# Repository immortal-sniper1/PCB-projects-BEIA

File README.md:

# PCB-projects
 PCB project files and skematics

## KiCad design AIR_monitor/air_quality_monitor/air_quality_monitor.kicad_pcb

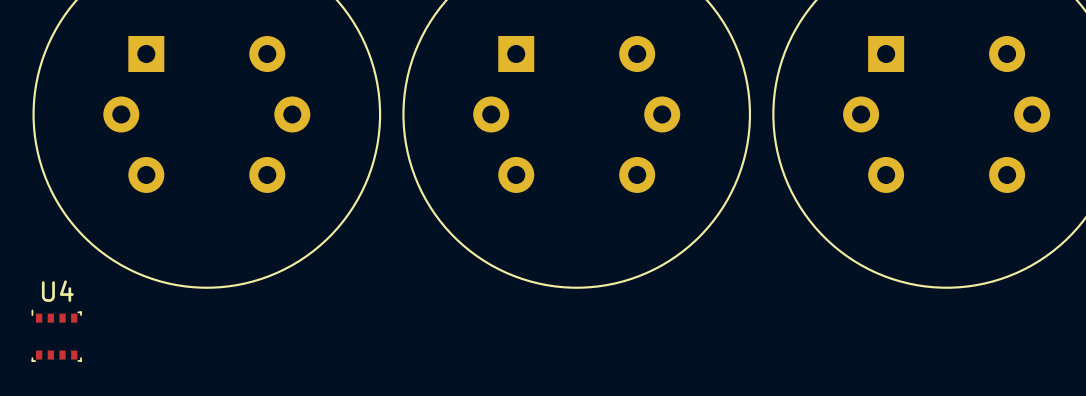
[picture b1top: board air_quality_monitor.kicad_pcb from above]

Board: 2 copper layers, 4 parts (0 on the bottom side), 5 nets, no tracks yet.

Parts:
U1: MQ-131; MQ-6
U2: MQ-136; MQ-6
U3: MQ-5/7/9; MQ-6
U4: BME280; Bosch_LGA-8_2.5x2.5mm_P0.65mm_ClockwisePinNumbering

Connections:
+5V: U1.2 (VH+), U1.4 (A2), U1.6 (A1), U2.2 (VH+), U2.4 (A2), U2.6 (A1), U3.2 (VH+), U3.4 (A2), U3.6 (A1)
GND: U1.5 (VH-), U2.5 (VH-), U3.5 (VH-), U4.1 (GND), U4.7 (GND)
unnamed: U1.1 (B1), U1.3 (B2)
unnamed: U2.1 (B1), U2.3 (B2)
unnamed: U3.1 (B1), U3.3 (B2)

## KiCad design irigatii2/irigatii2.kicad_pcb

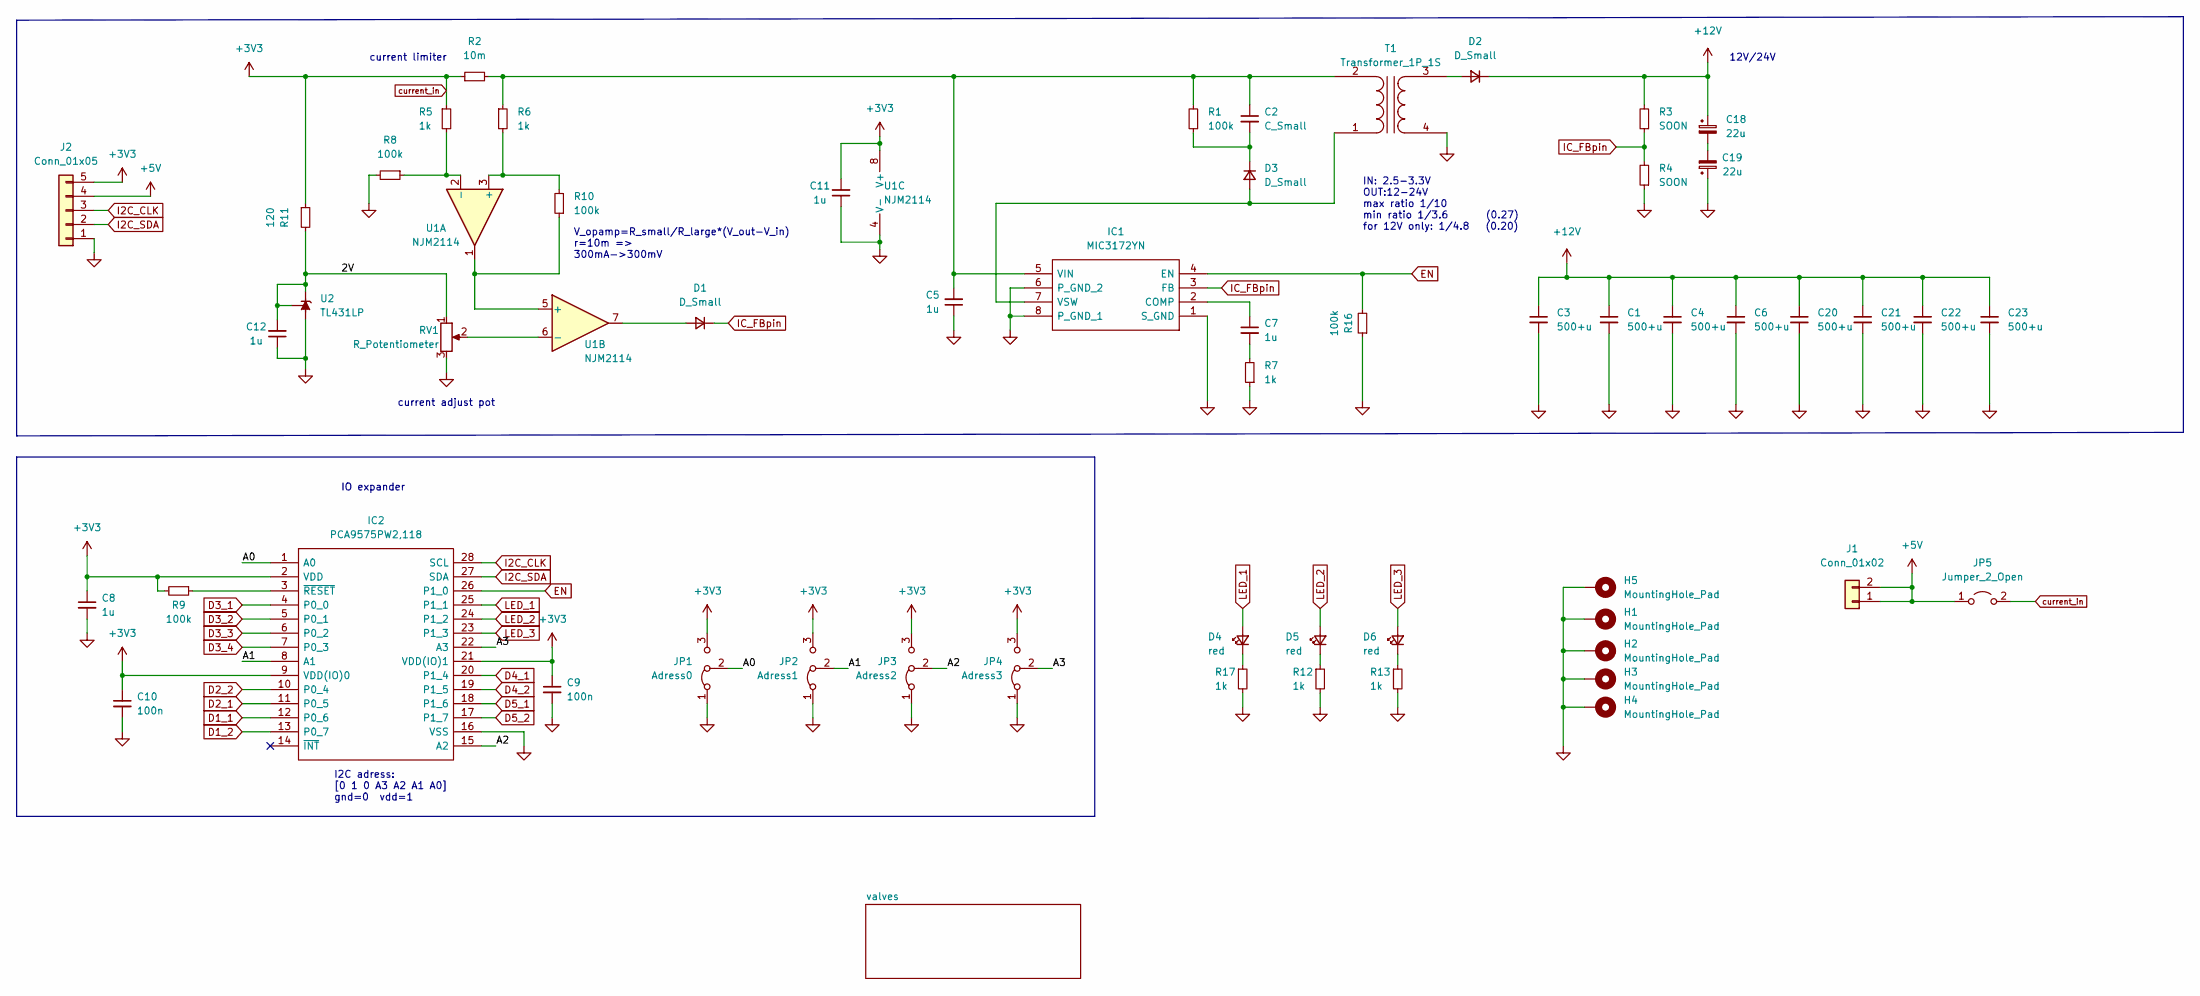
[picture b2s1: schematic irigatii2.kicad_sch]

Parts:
C1, C3, C4, C6, C20, C21, C22, C23: 500+u; CP_Radial_D13.0mm_P5.00mm
C2: C_Small; C_Disc_D4.3mm_W1.9mm_P5.00mm
C5: 1u; C_Disc_D4.3mm_W1.9mm_P5.00mm
C7, C11, C12: 1u; C_Disc_D3.8mm_W2.6mm_P2.50mm
C8: 1u; C_0805_2012Metric_Pad1.18x1.45mm_HandSolder
C9, C10: 100n; C_0805_2012Metric_Pad1.18x1.45mm_HandSolder
C18, C19: 22u; CP_Radial_D5.0mm_P2.00mm
D1, D3: D_Small; D_A-405_P5.08mm_Vertical_KathodeUp
D2: D_Small; D_A-405_P10.16mm_Horizontal
D4, D5, D6: red; LED_D5.0mm
H1, H2, H3, H4, H5: MountingHole_Pad; MountingHole_3.2mm_M3_Pad_TopBottom
IC1: MIC3172YN; DIP762W57P254L952H343Q8N; Mouser Part Number 998-MIC3172YN
IC2: PCA9575PW2,118; SOP65P640X110-28N; Mouser Part Number 771-PCA9575PW2,118
J1: Conn_01x02; PinHeader_1x02_P2.54mm_Vertical
J2: Conn_01x05; PinHeader_1x05_P2.54mm_Vertical
JP1: Adress0; SolderJumper-3_P1.3mm_Bridged12_Pad1.0x1.5mm
JP2: Adress1; SolderJumper-3_P1.3mm_Bridged12_Pad1.0x1.5mm
JP3: Adress2; SolderJumper-3_P1.3mm_Bridged12_Pad1.0x1.5mm
JP4: Adress3; SolderJumper-3_P1.3mm_Bridged12_Pad1.0x1.5mm
JP5: Jumper_2_Open; SolderJumper-2_P1.3mm_Open_Pad1.0x1.5mm
R1, R8, R9, R10, R16: 100k; R_Axial_DIN0204_L3.6mm_D1.6mm_P5.08mm_Vertical
R2: 10m; R_Axial_DIN0207_L6.3mm_D2.5mm_P10.16mm_Horizontal
R3, R4: SOON; R_Axial_DIN0207_L6.3mm_D2.5mm_P10.16mm_Horizontal
R5, R6, R7, R12, R13, R17: 1k; R_Axial_DIN0204_L3.6mm_D1.6mm_P5.08mm_Vertical
R11: 120; R_Axial_DIN0204_L3.6mm_D1.6mm_P5.08mm_Vertical
RV1: R_Potentiometer; Potentiometer_ACP_CA9-V10_Vertical
T1: Transformer_1P_1S; TRANSFORMER
U1: NJM2114; DIP-8_W7.62mm_LongPads
U2: TL431LP; TO-92_Inline

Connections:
+5V: J1.1, J1.2, J2.4, JP5.1 (A)
+12V: C1.1, C3.1, C4.1, C6.1, C18.1, C20.1, C21.1, C22.1, C23.1, D2.1 (K), R3.2; also elsewhere on the board
/2V: C12.2, R11.2, RV1.1, U2.1 (REF), U2.3 (K)
/A0: IC2.1 (A0), JP1.2 (C)
/A1: IC2.8 (A1), JP2.2 (C)
/A2: IC2.15 (A2), JP3.2 (C)
/A3: IC2.22 (A3), JP4.2 (C)
D1_1: IC2.12 (P0_6); also elsewhere on the board
D1_2: IC2.13 (P0_7); also elsewhere on the board
D2_1: IC2.11 (P0_5); also elsewhere on the board
D2_2: IC2.10 (P0_4); also elsewhere on the board
D3_1: IC2.4 (P0_0); also elsewhere on the board
D3_2: IC2.5 (P0_1); also elsewhere on the board
D3_3: IC2.6 (P0_2); also elsewhere on the board
D3_4: IC2.7 (P0_3); also elsewhere on the board
D4_1: IC2.20 (P1_4); also elsewhere on the board
D4_2: IC2.19 (P1_5); also elsewhere on the board
D5_1: IC2.18 (P1_6); also elsewhere on the board
D5_2: IC2.17 (P1_7); also elsewhere on the board
EN: IC1.4 (EN), IC2.26 (P1_0), R16.2
GND: C1.2, C3.2, C4.2, C5.1, C6.2, C8.2, C9.2, C10.2, C11.1, C12.1, C19.1, C20.2, C21.2, C22.2, C23.2, H1.1, H2.1, H3.1, H4.1, H5.1, IC1.1 (S_GND), IC1.6 (P_GND_2), IC1.8 (P_GND_1), IC2.16 (VSS), J2.1, JP1.1 (A), JP2.1 (A), JP3.1 (A), JP4.1 (A), R4.1, R7.1, R8.2, R12.2, R13.2, R16.1, R17.2, RV1.3, T1.4 (SB), U1.4 (V-), U2.2 (A); also elsewhere on the board
I2C_CLK: IC2.28 (SCL), J2.3
I2C_SDA: IC2.27 (SDA), J2.2
IC_FBpin: D1.1 (K), IC1.3 (FB), R3.1, R4.2
LED_1: D4.2 (A), IC2.25 (P1_1)
LED_2: D5.2 (A), IC2.24 (P1_2)
LED_3: D6.2 (A), IC2.23 (P1_3)
unnamed: C2.1, C5.2, IC1.5 (VIN), R1.2, R2.2, R6.1, T1.2 (AB)
unnamed: C2.2, D3.1 (K), R1.1
unnamed: C7.1, IC1.2 (COMP)
unnamed: C7.2, R7.2
unnamed: C18.2, C19.2
unnamed: D1.2 (A), U1.7
unnamed: D2.2 (A), T1.3 (SA)
unnamed: D3.2 (A), IC1.7 (VSW), T1.1 (AA)
unnamed: D4.1 (K), R17.1
unnamed: D5.1 (K), R12.1
unnamed: D6.1 (K), R13.1
unnamed: IC2.3 (~RESET), R9.1
unnamed: R5.2, R8.1, U1.2 (-)
unnamed: R10.1, U1.1, U1.5 (+)
unnamed: R6.2, R10.2, U1.3 (+)
unnamed: RV1.2, U1.6 (-)
current_in: C8.1, C9.1, C10.1, C11.2, IC2.2 (VDD), IC2.9 (VDD(IO)0), IC2.21 (VDD(IO)1), J2.5, JP1.3 (B), JP2.3 (B), JP3.3 (B), JP4.3 (B), JP5.2 (B), R2.1, R5.1, R9.2, R11.1, U1.8 (V+)

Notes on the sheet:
current adjust pot
V_opamp=R_small/R_large*(V_out-V_in) r=10m => 300mA->300mV
current limiter
I2C adress: [0 1 0 A3 A2 A1 A0] gnd=0 vdd=1
12V/24V
IN: 2.5-3.3V OUT:12-24V max ratio 1/10 min ratio 1/3.6 (0.27) for 12V only: 1/4.8 (0.20)
IO expander

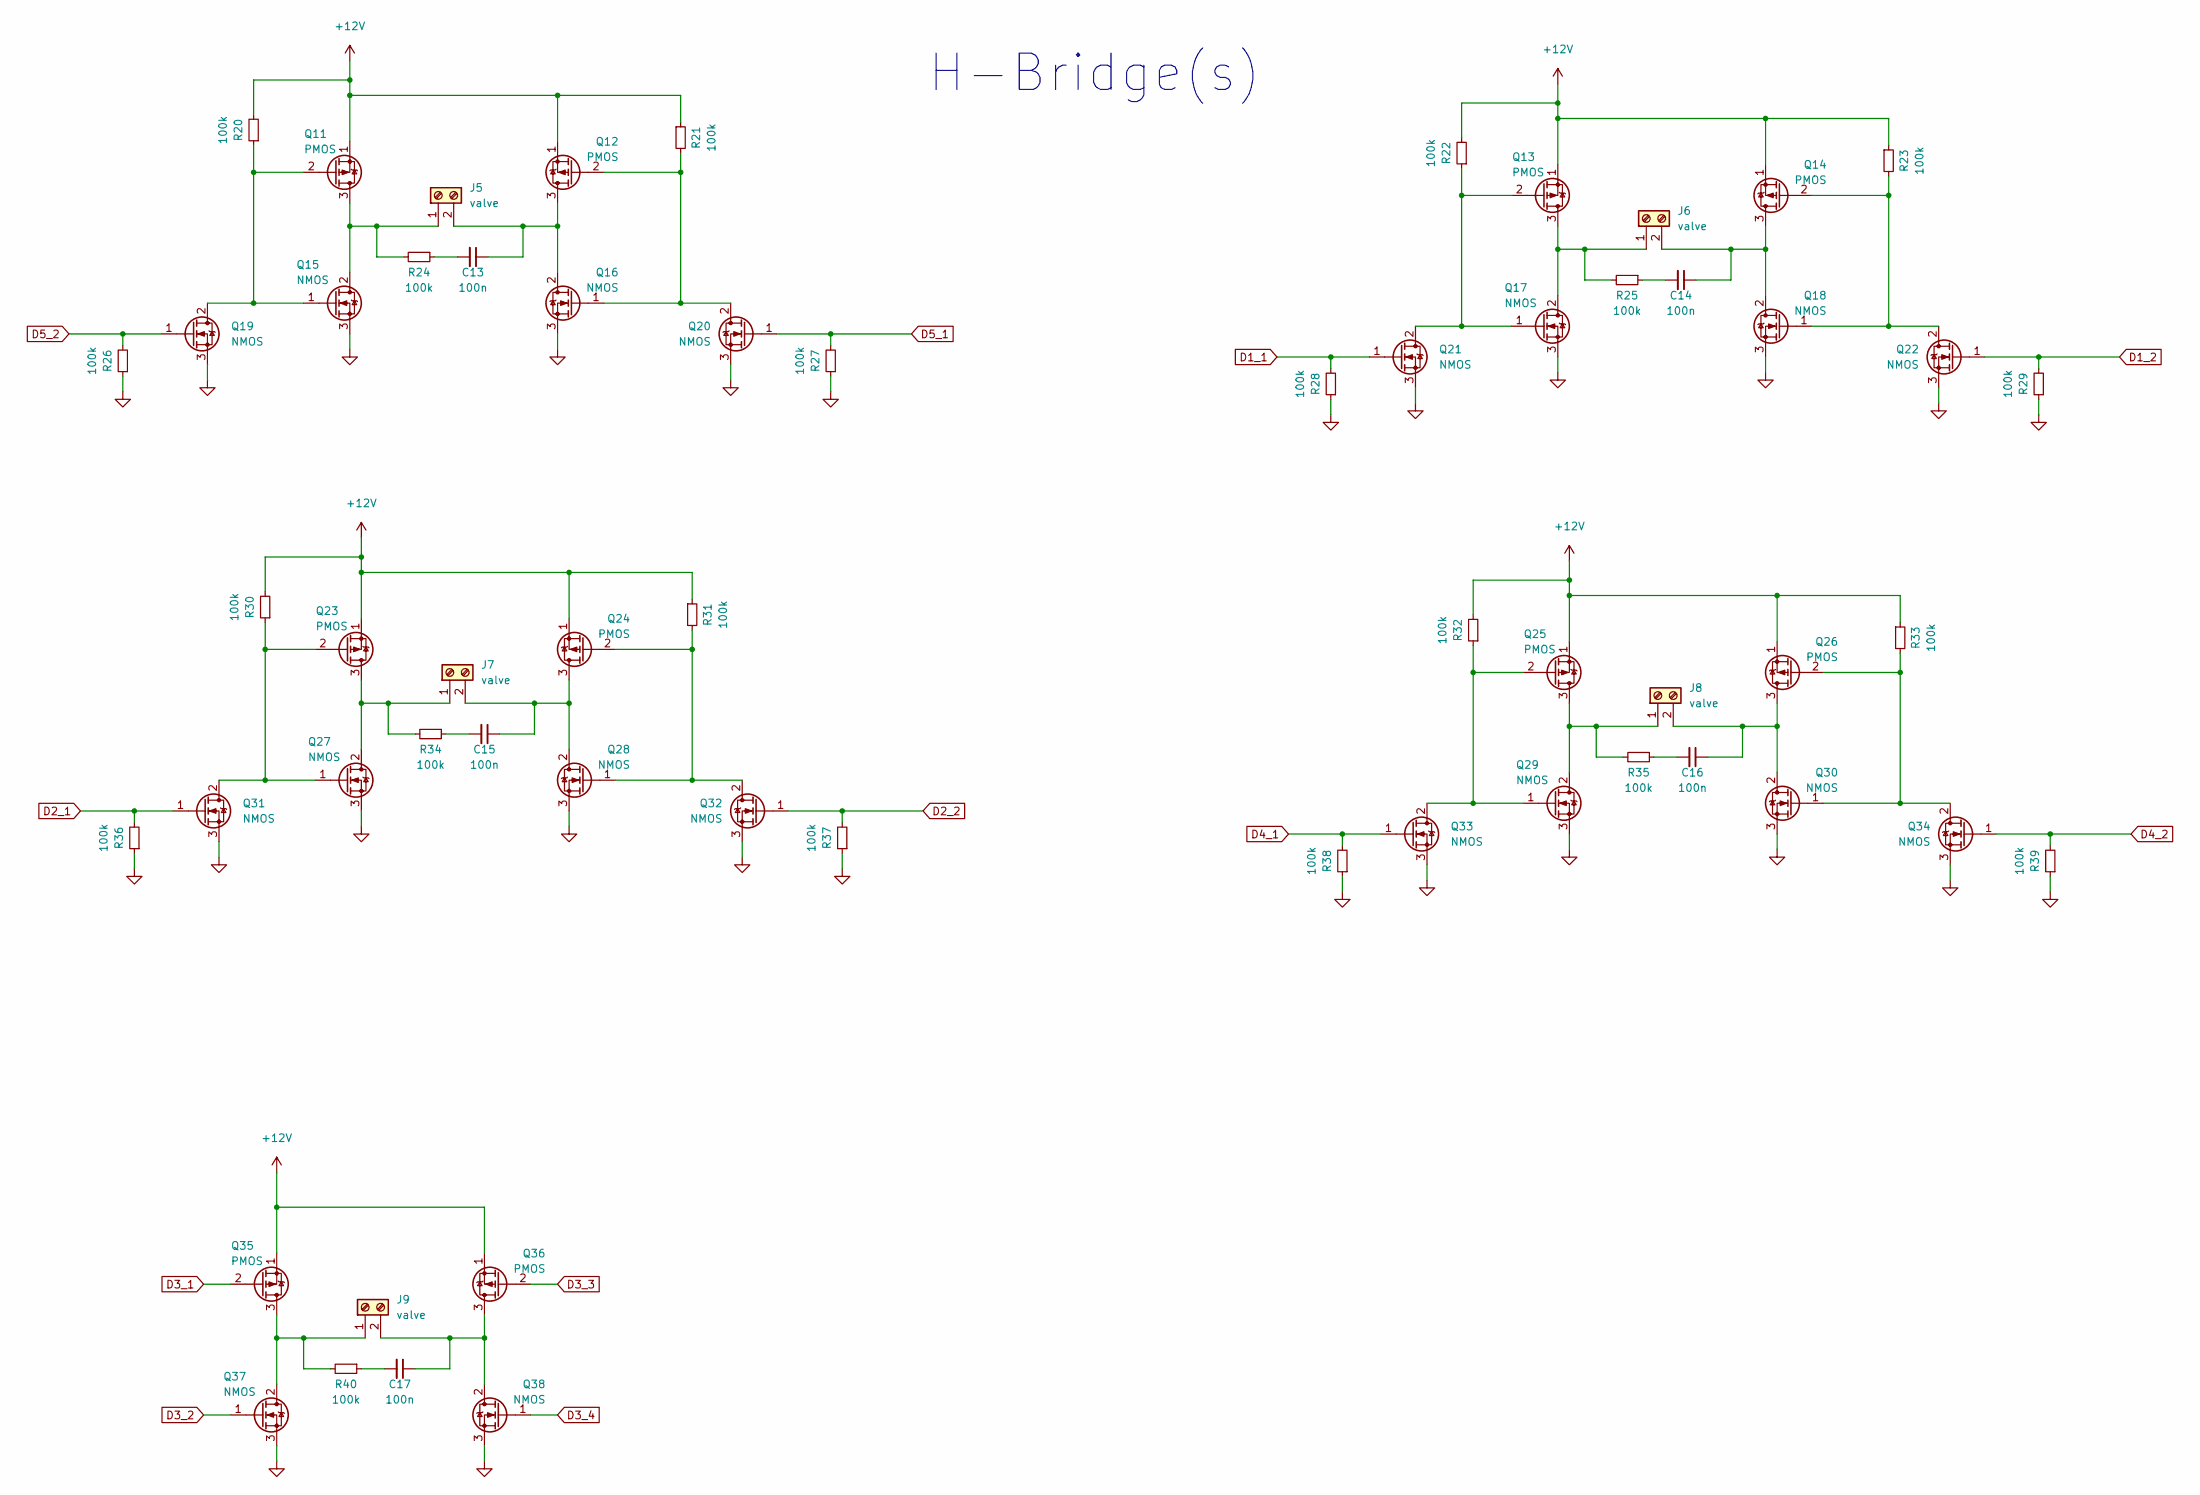
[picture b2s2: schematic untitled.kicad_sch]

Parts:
C13, C14, C15, C16, C17: 100n; C_Disc_D3.8mm_W2.6mm_P2.50mm
J5, J6, J7, J8, J9: valve; TerminalBlock_Altech_AK300-2_P5.00mm
Q11, Q12, Q13, Q14, Q23, Q24, Q25, Q26, Q35, Q36: PMOS; TO-92_Wide
Q15, Q16, Q17, Q18, Q19, Q20, Q21, Q22, Q27, Q28, Q29, Q30, Q31, Q32, Q33, Q34, Q37, Q38: NMOS; TO-92_Inline_Wide
R20, R21, R22, R23, R24, R25, R26, R27, R28, R29, R30, R31, R32, R33, R35, R36, R37, R38, R39, R40: 100k; R_Axial_DIN0204_L3.6mm_D1.6mm_P5.08mm_Vertical
R34: 100k; R_Axial_DIN0204_L3.6mm_D1.6mm_P5.08mm_Horizontal

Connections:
+12V: Q11.1 (S), Q12.1 (S), Q13.1 (S), Q14.1 (S), Q23.1 (S), Q24.1 (S), Q25.1 (S), Q26.1 (S), Q35.1 (S), Q36.1 (S), R20.2, R21.1, R22.2, R23.1, R30.2, R31.1, R32.2, R33.1; also elsewhere on the board
D1_1: Q21.1 (G), R28.2; also elsewhere on the board
D1_2: Q22.1 (G), R29.2; also elsewhere on the board
D2_1: Q31.1 (G), R36.2; also elsewhere on the board
D2_2: Q32.1 (G), R37.2; also elsewhere on the board
D3_1: Q35.2 (G); also elsewhere on the board
D3_2: Q37.1 (G); also elsewhere on the board
D3_3: Q36.2 (G); also elsewhere on the board
D3_4: Q38.1 (G); also elsewhere on the board
D4_1: Q33.1 (G), R38.2; also elsewhere on the board
D4_2: Q34.1 (G), R39.2; also elsewhere on the board
D5_1: Q20.1 (G), R27.2; also elsewhere on the board
D5_2: Q19.1 (G), R26.2; also elsewhere on the board
GND: Q15.3 (S), Q16.3 (S), Q17.3 (S), Q18.3 (S), Q19.3 (S), Q20.3 (S), Q21.3 (S), Q22.3 (S), Q27.3 (S), Q28.3 (S), Q29.3 (S), Q30.3 (S), Q31.3 (S), Q32.3 (S), Q33.3 (S), Q34.3 (S), Q37.3 (S), Q38.3 (S), R26.1, R27.1, R28.1, R29.1, R36.1, R37.1, R38.1, R39.1; also elsewhere on the board
unnamed: C13.1, J5.2, Q12.3 (D), Q16.2 (D)
unnamed: C13.2, R24.1
unnamed: C14.1, J6.2, Q14.3 (D), Q18.2 (D)
unnamed: C14.2, R25.1
unnamed: C15.1, J7.2, Q24.3 (D), Q28.2 (D)
unnamed: C15.2, R34.1
unnamed: C16.1, J8.2, Q26.3 (D), Q30.2 (D)
unnamed: C16.2, R35.1
unnamed: C17.1, J9.2, Q36.3 (D), Q38.2 (D)
unnamed: C17.2, R40.1
unnamed: J5.1, Q11.3 (D), Q15.2 (D), R24.2
unnamed: J6.1, Q13.3 (D), Q17.2 (D), R25.2
unnamed: J7.1, Q23.3 (D), Q27.2 (D), R34.2
unnamed: J8.1, Q25.3 (D), Q29.2 (D), R35.2
unnamed: J9.1, Q35.3 (D), Q37.2 (D), R40.2
unnamed: Q11.2 (G), Q15.1 (G), Q19.2 (D), R20.1
unnamed: Q12.2 (G), Q16.1 (G), Q20.2 (D), R21.2
unnamed: Q13.2 (G), Q17.1 (G), Q21.2 (D), R22.1
unnamed: Q14.2 (G), Q18.1 (G), Q22.2 (D), R23.2
unnamed: Q23.2 (G), Q27.1 (G), Q31.2 (D), R30.1
unnamed: Q24.2 (G), Q28.1 (G), Q32.2 (D), R31.2
unnamed: Q25.2 (G), Q29.1 (G), Q33.2 (D), R32.1
unnamed: Q26.2 (G), Q30.1 (G), Q34.2 (D), R33.2

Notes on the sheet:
H-Bridge(s)

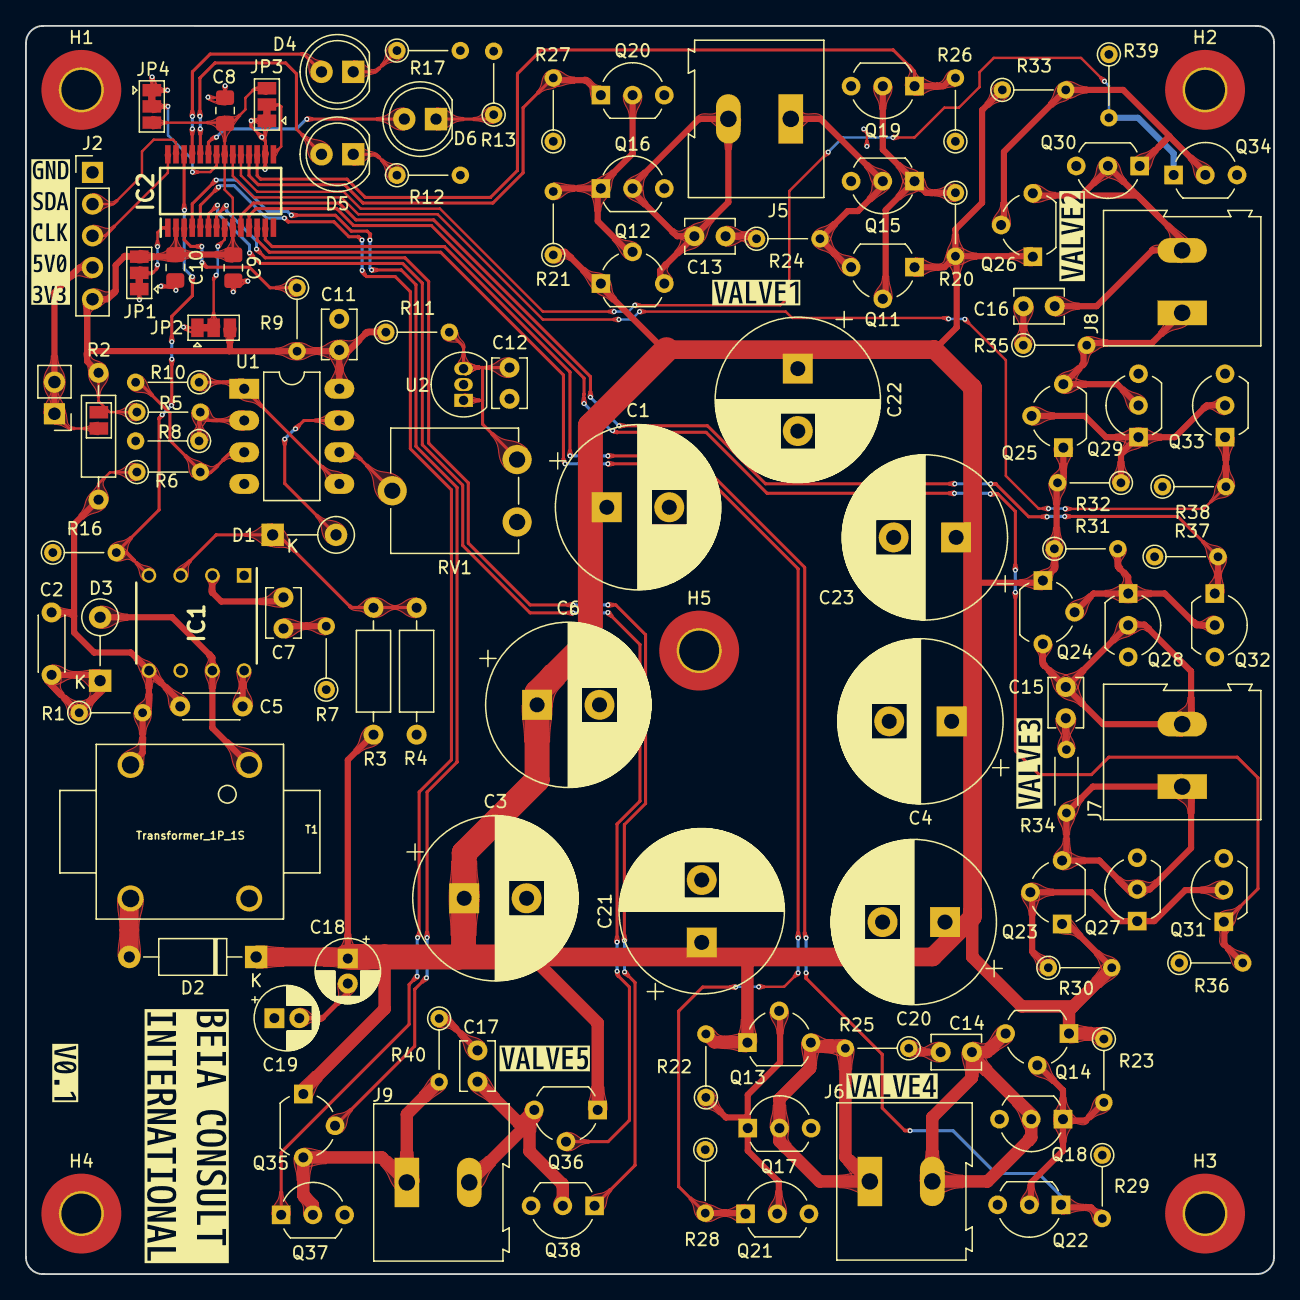
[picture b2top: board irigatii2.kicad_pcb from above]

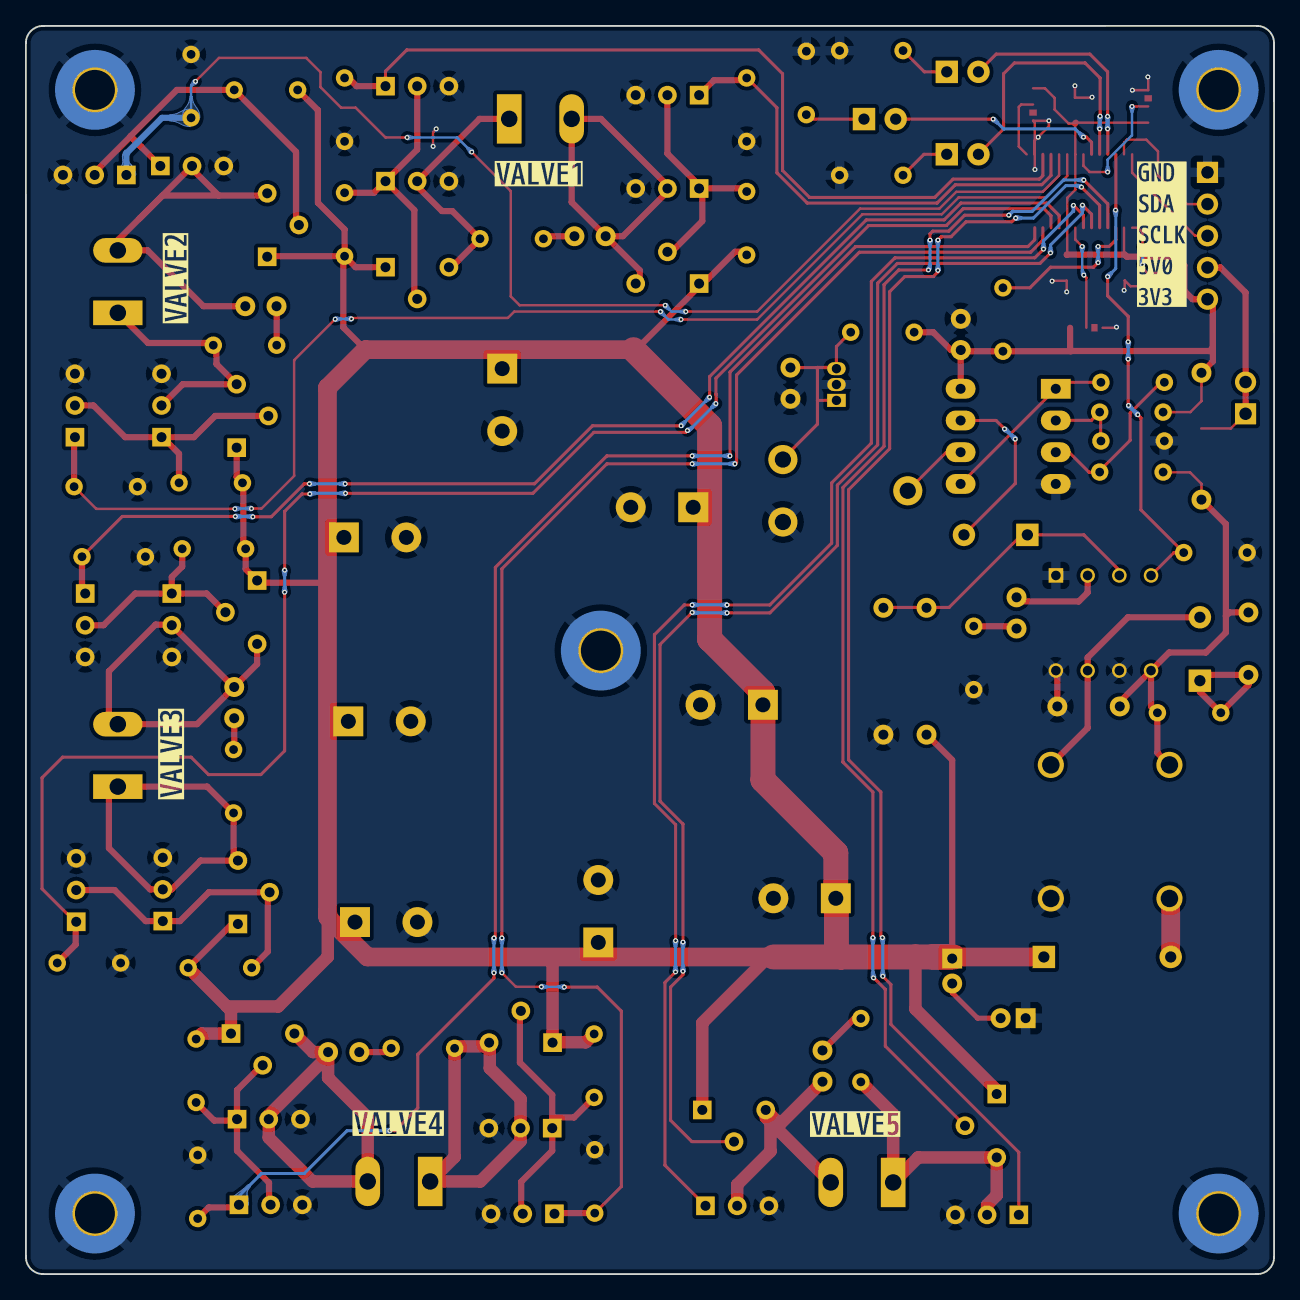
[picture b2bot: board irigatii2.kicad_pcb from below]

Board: 2 copper layers, 100.0 x 100.0 mm, 130 parts (6 on the bottom side), 67 nets.

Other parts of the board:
kibuzzard-633BE47A: G***; kibuzzard-633BE47A
kibuzzard-633BE88B: G***; kibuzzard-633BE88B
kibuzzard-633BFC8D, kibuzzard-633BFC8D#2: G***; kibuzzard-633BFC8D
kibuzzard-633BFC9A, kibuzzard-633BFC9A#2: G***; kibuzzard-633BFC9A
kibuzzard-633BFCC9, kibuzzard-633BFCC9#2: G***; kibuzzard-633BFCC9
kibuzzard-633BFCF4, kibuzzard-633BFCF4#2: G***; kibuzzard-633BFCF4
kibuzzard-633BFD23, kibuzzard-633BFD23#2: G***; kibuzzard-633BFD23
kibuzzard-633BFE0C: G***; kibuzzard-633BFE0C
kibuzzard-633BFE28: G***; kibuzzard-633BFE28

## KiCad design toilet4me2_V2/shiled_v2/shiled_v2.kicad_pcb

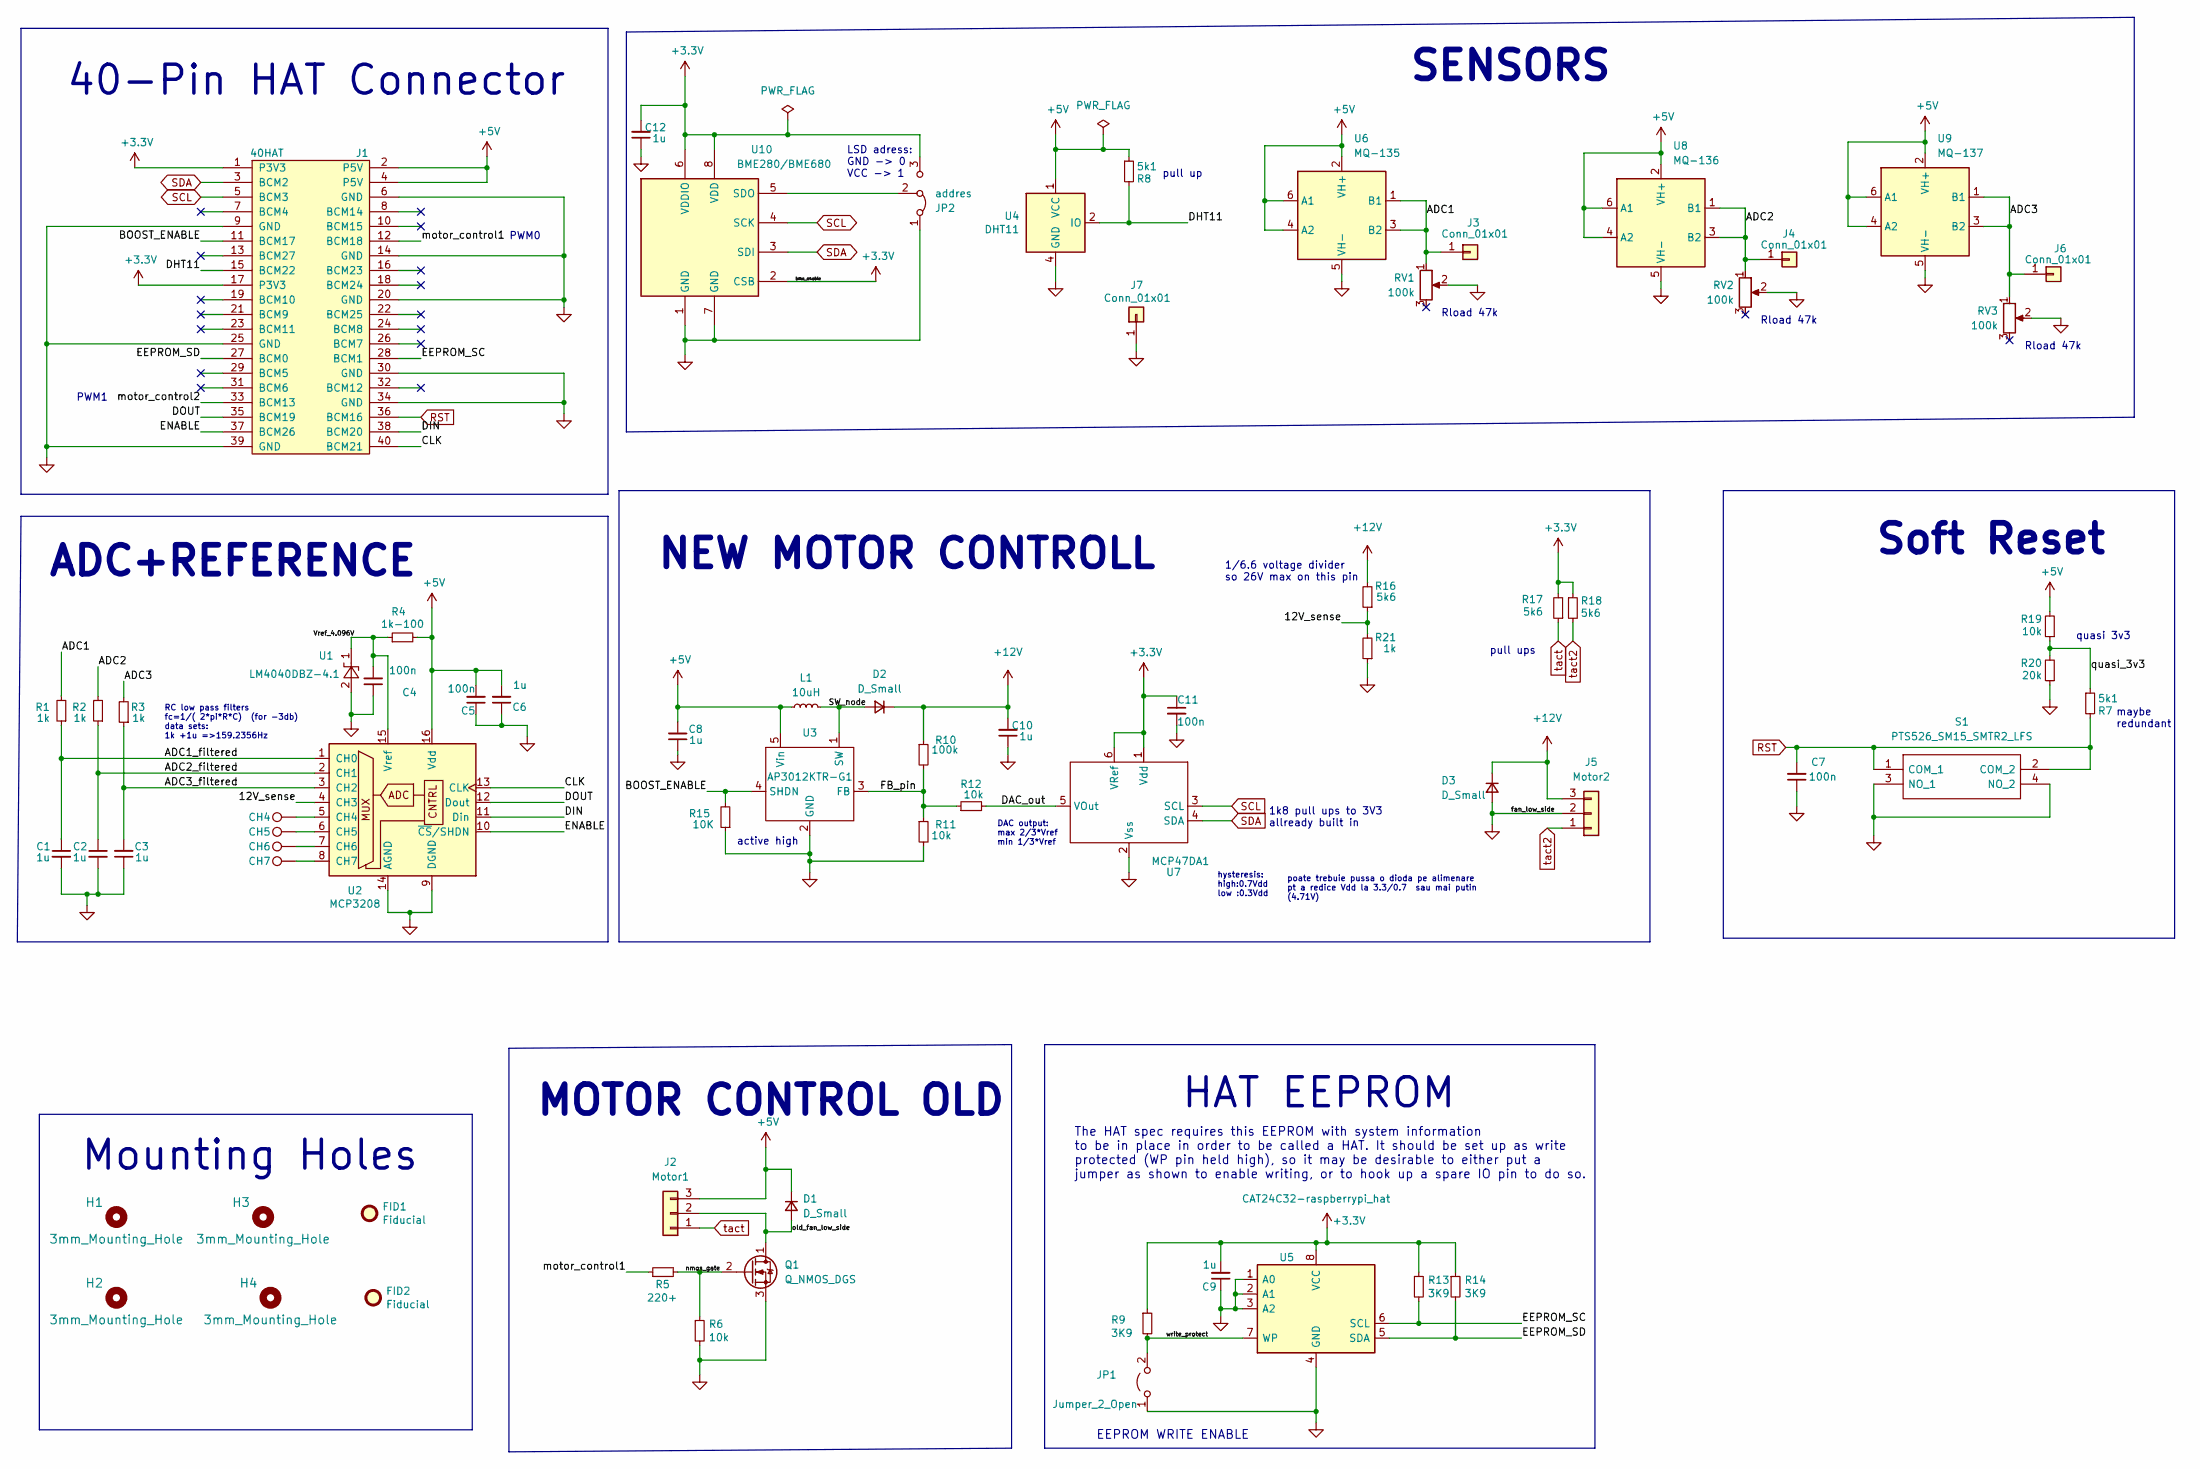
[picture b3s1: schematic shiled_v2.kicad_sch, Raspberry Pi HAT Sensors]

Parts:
C1, C2, C3, C6, C8, C9, C10, C12: 1u; C_0805_2012Metric_Pad1.18x1.45mm_HandSolder
C4, C5, C7, C11: 100n; C_0805_2012Metric_Pad1.18x1.45mm_HandSolder
CH4, CH5, CH6, CH7: -; TestPoint_THTPad_D1.0mm_Drill0.5mm
D1, D2, D3: D_Small; D_SOD-123
FID1: Fiducial; Fiducial_1.5mm_Mask3mm
FID2: Fiducial; WEEE-Logo_4.2x6mm_SilkScreen
H1, H2, H3, H4: 3mm_Mounting_Hole; NPTH_3mm_ID
J1: 40HAT; PinSocket_2x20_P2.54mm_Vertical
J2: Motor1; PinHeader_1x03_P2.54mm_Vertical
J3, J4, J6, J7: Conn_01x01; PinHeader_1x01_P2.54mm_Vertical
J5: Motor2; PinHeader_1x03_P2.54mm_Vertical
JP1: Jumper_2_Open; PinHeader_1x02_P2.54mm_Vertical
JP2: addres; SolderJumper-3_P1.3mm_Bridged12_Pad1.0x1.5mm
L1: 10uH; L_Taiyo-Yuden_MD-5050
Q1: Q_NMOS_DGS; TO-92_HandSolder
R1, R2, R3, R21: 1k; R_0805_2012Metric_Pad1.20x1.40mm_HandSolder
R4: 1k-100; R_0805_2012Metric_Pad1.20x1.40mm_HandSolder
R5: 220+; R_Axial_DIN0204_L3.6mm_D1.6mm_P2.54mm_Vertical
R6: 10k; R_Axial_DIN0204_L3.6mm_D1.6mm_P2.54mm_Vertical
R7, R8: 5k1; R_0805_2012Metric_Pad1.20x1.40mm_HandSolder
R9, R13, R14: 3K9; R_0805_2012Metric_Pad1.20x1.40mm_HandSolder
R10: 100k; R_0805_2012Metric_Pad1.20x1.40mm_HandSolder
R11, R12, R19: 10k; R_0805_2012Metric_Pad1.20x1.40mm_HandSolder
R15: 10K; R_0805_2012Metric_Pad1.20x1.40mm_HandSolder
R16, R17, R18: 5k6; R_0805_2012Metric_Pad1.20x1.40mm_HandSolder
R20: 20k; R_0805_2012Metric_Pad1.20x1.40mm_HandSolder
RV1, RV2, RV3: 100k; Potentiometer_Piher_PT-10-V05_Vertical
S1: PTS526_SM15_SMTR2_LFS; PTS526SM15SMTR2LFS; Mouser Part Number 611-PTS526SM15SMTR2L
U1: LM4040DBZ-4.1; SOT-23
U2: MCP3208; SOIC-16_3.9x9.9mm_P1.27mm
U3: AP3012KTR-G1; SOT-23-5_HandSoldering
U4: DHT11; Aosong_DHT11_5.5x12.0_P2.54mm
U5: CAT24C32-raspberrypi_hat; TSSOP-8_4.4x3mm_P0.65mm
U6: MQ-135; MQ-6
U7: MCP47DA1; SOT-23-6_Handsoldering
U8: MQ-136; MQ-6
U9: MQ-137; MQ-6
U10: BME280/BME680; Bosch_LGA-8_2.5x2.5mm_P0.65mm_ClockwisePinNumbering

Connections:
+3V3: C9.2, C11.1, C12.2, J1.1 (P3V3), J1.17 (P3V3), JP2.3 (B), R9.1, R13.1, R14.1, R17.2, R18.1, U5.8 (VCC), U7.1 (Vdd), U7.6 (VRef), U10.2 (CSB), U10.6 (VDDIO), U10.8 (VDD)
+5V: C5.2, C6.2, C8.2, D1.1 (K), J1.2 (P5V), J1.4 (P5V), J2.3, L1.1, R4.2, R8.1, R19.2, U2.16 (Vdd), U3.5 (Vin), U4.1 (VCC), U6.2 (VH+), U6.4 (A2), U6.6 (A1), U8.2 (VH+), U8.4 (A2), U8.6 (A1), U9.2 (VH+), U9.4 (A2), U9.6 (A1)
+12V: C10.2, D2.1 (K), D3.1 (K), J5.3, R10.1, R16.2
/12V_sense: R16.1, R21.2, U2.4 (CH3)
/ADC1: J3.1, R1.2, RV1.1, U6.1 (B1), U6.3 (B2)
/ADC1_filtered: C1.1, R1.1, U2.1 (CH0)
/ADC2: J4.1, R2.2, RV2.1, U8.1 (B1), U8.3 (B2)
/ADC2_filtered: C2.1, R2.1, U2.2 (CH1)
/ADC3: J6.1, R3.2, RV3.1, U9.1 (B1), U9.3 (B2)
/ADC3_filtered: C3.2, R3.1, U2.3 (CH2)
/BOOST_ENABLE: J1.11 (BCM17), R15.2, U3.4 (SHDN)
/CLK: J1.40 (BCM21), U2.13 (CLK)
/DAC_out: R12.2, U7.5 (VOut)
/DHT11: J1.15 (BCM22), R8.2, U4.2 (IO)
/DIN: J1.38 (BCM20), U2.11 (Din)
/DOUT: J1.35 (BCM19), U2.12 (Dout)
/EEPROM_SC: J1.28 (BCM1), R13.2, U5.6 (SCL)
/EEPROM_SD: J1.27 (BCM0), R14.2, U5.5 (SDA)
/ENABLE: J1.37 (BCM26), U2.10 (~CS/SHDN)
/FB_pin: R10.2, R11.1, R12.1, U3.3 (FB)
/SW_node: D2.2 (A), L1.2, U3.1 (SW)
/Vref_4.096V: C4.2, R4.1, U1.1 (K), U2.15 (Vref)
/motor_control1: J1.12 (BCM18), R5.1
/motor_control2: J1.33 (BCM13)
/nmos_gate: Q1.2 (G), R5.2, R6.1
/old_fan_low_side: D1.2 (A), J2.2, Q1.1 (D)
/quasi_3v3: R7.1, R19.1, R20.2
/write_protect: JP1.2 (B), R9.2, U5.7 (WP)
GND: C1.2, C2.2, C3.1, C4.1, C5.1, C6.1, C7.1, C8.1, C9.1, C10.1, C11.2, C12.1, D3.2 (A), J1.6 (GND), J1.9 (GND), J1.14 (GND), J1.20 (GND), J1.25 (GND), J1.30 (GND), J1.34 (GND), J1.39 (GND), J5.2, J7.1, JP1.1 (A), JP2.1 (A), Q1.3 (S), R6.2, R11.2, R15.1, R20.1, R21.1, RV1.2, RV2.2, RV3.2, S1.3 (NO_1), S1.4 (NO_2), U1.2 (A), U2.9 (DGND), U2.14 (AGND), U3.2 (GND), U4.4 (GND), U5.1 (A0), U5.2 (A1), U5.3 (A2), U5.4 (GND), U6.5 (VH-), U7.2 (Vss), U8.5 (VH-), U9.5 (VH-), U10.1 (GND), U10.7 (GND)
unnamed: CH4.1, U2.5 (CH4)
unnamed: CH5.1, U2.6 (CH5)
unnamed: CH6.1, U2.7 (CH6)
unnamed: CH7.1, U2.8 (CH7)
unnamed: JP2.2 (C), U10.5 (SDO)
RST: C7.2, J1.36 (BCM16), R7.2, S1.1 (COM_1), S1.2 (COM_2)
SCL: J1.5 (BCM3), U7.3 (SCL), U10.4 (SCK)
SDA: J1.3 (BCM2), U7.4 (SDA), U10.3 (SDI)
tact: J2.1, R17.1
tact2: J5.1, R18.2

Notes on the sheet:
NEW MOTOR CONTROLL
Rload 47k
The HAT spec requires this EEPROM with system information to be in place in order to be called a HAT. It should be set up as write protected (WP pin held high), so it may be desirable to either put a jumper as shown to enable writing, or to hook up a spare IO pin to do so.
PWM0
Soft Reset
quasi 3v3
PWM1
ADC+REFERENCE
hysteresis: high:0.7Vdd low :0.3Vdd
SENSORS
active high
1k8 pull ups to 3V3 allready built in
maybe redundant
40-Pin HAT Connector
Mounting Holes
HAT EEPROM
LSD adress: GND -> 0 VCC -> 1
EEPROM WRITE ENABLE
pull up
pull ups
poate trebuie pussa o dioda pe alimenare pt a redice Vdd la 3.3/0.7 sau mai putin (4.71V)
DAC output: max 2/3*Vref min 1/3*Vref
1/6.6 voltage divider so 26V max on this pin
MOTOR CONTROL OLD
RC low pass filters fc=1/( 2*pi*R*C) (for -3db) data sets: 1k +1u =>159.2356Hz
